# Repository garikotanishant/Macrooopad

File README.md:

# Macrooopad
A 10 key, 2 rotary encoder, macropad designed and built by me. With each key and rotary encoder being able to be addressable so I can set it to whatever command (volume, open specific app, brightness, etc). Useful for quickly doing actions.

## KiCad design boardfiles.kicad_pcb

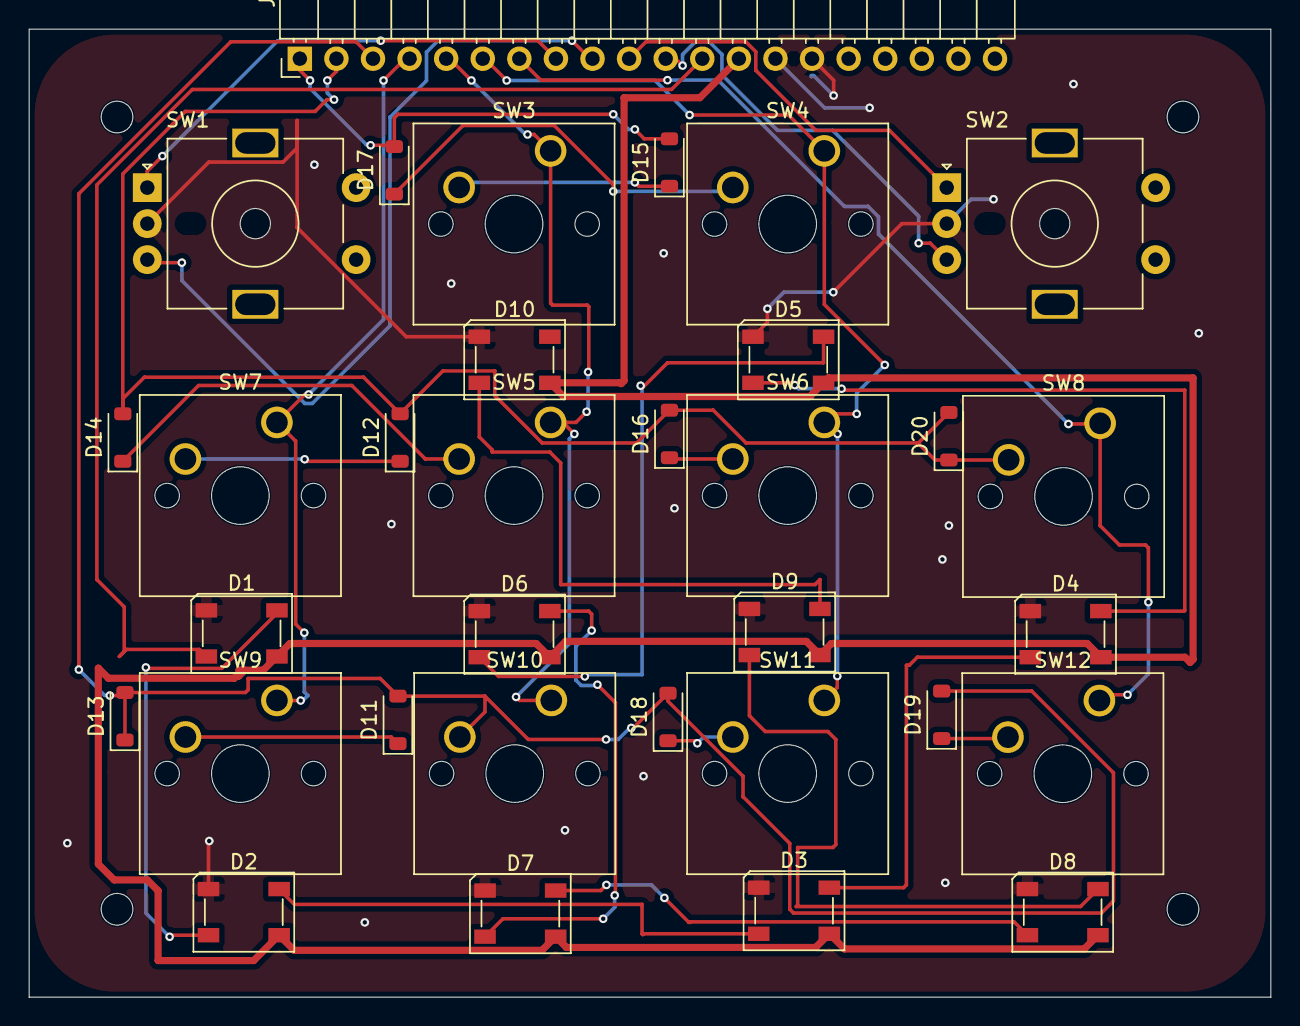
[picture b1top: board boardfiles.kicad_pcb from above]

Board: 2 copper layers, 86.2 x 67.2 mm, 33 parts (0 on the bottom side), 31 nets.

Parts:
D1, D2, D3, D4, D5, D6, D7, D8, D9, D10: SK6812; LED_SK6812_PLCC4_5.0x5.0mm_P3.2mm
D11, D12, D13, D14, D15, D16, D17, D18, D19, D20: 1N4148W; D_SOD-123
J1: Conn_01x20; PinHeader_1x20_P2.54mm_Horizontal
SW1, SW2: RotaryEncoder; RotaryEncoder_Alps_EC11E-Switch_Vertical_H20mm_MountingHoles
SW3, SW4, SW5, SW6, SW7, SW8, SW9, SW10, SW11, SW12: SW_Push; SW_Cherry_MX_1.00u_PCB

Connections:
+3V3: D1.3 (VDD), D2.3 (VDD), D3.3 (VDD), D4.3 (VDD), D5.3 (VDD), D6.3 (VDD), D7.3 (VDD), D8.3 (VDD), D9.3 (VDD), D10.3 (VDD), J1.13
/COL0: J1.4, SW7.1, SW9.1
/COL1: J1.5, SW3.1, SW5.1, SW10.1
/COL2: J1.6, SW4.1, SW6.1, SW11.1
/COL3: J1.7, SW8.1, SW12.1
/ENC_L_A: J1.8, SW1.A
/ENC_L_B: J1.9, SW1.B
/ENC_R_A: J1.10, SW2.A
/ENC_R_B: J1.11, SW2.B
/RGB: D1.2 (DIN), J1.12
/ROW0: D15.2 (A), D17.2 (A), J1.1
/ROW1: D12.2 (A), D14.2 (A), D16.2 (A), D20.1 (K), D20.2 (A), J1.2, SW8.2
/ROW2: D11.2 (A), D13.1 (K), D13.2 (A), D18.2 (A), D19.2 (A), J1.3, SW10.2
GND: D1.1 (VSS), D2.1 (VSS), D3.1 (VSS), D4.1 (VSS), D5.1 (VSS), D6.1 (VSS), D7.1 (VSS), D8.1 (VSS), D9.1 (VSS), D10.1 (VSS), J1.14, J1.15, SW1.C, SW2.C
unnamed: D1.4 (DOUT), D2.2 (DIN)
unnamed: D2.4 (DOUT), D3.2 (DIN)
unnamed: D3.4 (DOUT), D4.2 (DIN)
unnamed: D4.4 (DOUT), D5.2 (DIN)
unnamed: D5.4 (DOUT), D6.2 (DIN)
unnamed: D6.4 (DOUT), D7.2 (DIN)
unnamed: D7.4 (DOUT), D8.2 (DIN)
unnamed: D8.4 (DOUT), D9.2 (DIN)
unnamed: D9.4 (DOUT), D10.2 (DIN)
unnamed: D11.1 (K), SW9.2
unnamed: D12.1 (K), SW7.2
unnamed: D14.1 (K), SW5.2
unnamed: D15.1 (K), SW3.2
unnamed: D16.1 (K), SW6.2
unnamed: D17.1 (K), SW4.2
unnamed: D18.1 (K), SW11.2
unnamed: D19.1 (K), SW12.2

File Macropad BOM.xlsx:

Category | Qty required | Qty to Buy | References | Part/Desc | KiCad Footprint | Picked Part/MPN | Supplier | Link | Price per part | Shipping
PCB | 1.0 | 5.0 | PCB | Bare 2-layer PCB | N/A | macropad custom PCB | JLCPCB | https://cart.jlcpcb.com/quote?stencilLayer=2&stencilWidth=10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 | 2.0 | 3.3
Diode | 10.0 | 20.0 | D11, D12, D13, D14, D15, D16, D17, D18, D19, D20 | 1N4148W Switching diode | SOD-123 | DigiKey 6022450 | Digikey | 1N4148W SMC Diode Solutions | Single Diodes | DigiKey | 1.66 | 8.49
Switch | 10.0 | 12.0 | SW3, SW4, SW5, SW6, SW7, SW8, SW9, SW10, SW11, SW12 | MX-compatible mechanical keyboard switch, 1u | Cherry_MX_1.00u_PCB | K01 Switch Tactile 45g Pre-Lubed 5 Pins Hot Swap Pom Stem HMX Switches For Mx M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 | Aliexpress | https://www.aliexpress.us/item/3256809734880722.html?spm=a2g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 | 15.25 | 1.72
Keycap | 10.0 | 20.0 | Keycaps for SW3-SW12 | 1u MX-compatible keycaps | Fits Cherry MX cross stem | 20Pcs PBT Blank Keycap 1U 1X XDA Profile No Print Keycap Set for DIY Mechanical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 | Aliexpress | https://www.aliexpress.us/item/3256804794847948.html?spm=a2g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 | 4.39 | 1.72
RGB LED | 10.0 | 12.0 | D1, D2, D3, D4, D5, D6, D7, D8, D9, D10 | SK6812 addressable RGB LED | SK6812 | WS2812 SK6812 RGB Pixel Led Chip Individually Addressable WS2812B SK6812 RGBCW 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 | Aliexpress | https://www.aliexpress.us/item/3256805844520306.html?spm=a2g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 | 4.5 | 1.72
Rotary Encoder | 2.0 | 2.0 | SW1, SW2 | EC11-style rotary encoder, vertical, A/C/B pins | Alps EC11E | 2/10PCSEC11 rotary encoder Digital potentiometer, plum blossom, half axis, five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 | Aliexpress | https://www.aliexpress.us/item/3256808861665209.html?spm=a2g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 | 5.0 | 1.72
Header | 1.0 | 1.0 | J1 | 1x20 2.54mm right angle male pin header | 1x20 2.54mm Horizontal | 1x20 right angle male header | Aliexpress | https://www.aliexpress.us/item/2255800801798474.html?spm=a2g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 | 1.55 | 1.72
Cable | 1.0 | 1.0 | J1 to Pico | 20-wire Dupont/ribbon cable to external Raspberry Pi Pico | N/A | 20-pin dupont cable | Aliexpress | https://www.aliexpress.us/item/3256809464901432.html?spm=a2g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 | 2.77 | 1.72
Controller | 1.0 | 1.0 | External | Rasperry Pi Pico or compatible controller | External, not mounted on PCB | Raspberry Pi Pico Board RP2040 TYPE-C / MICRO Dual-Core 264KB ARM Low-Power Mic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 | Aliexpress | https://www.aliexpress.us/item/3256803486365836.html?spm=a2g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 | 2.97 | 1.72
Mounting | 4.0 | 4.0 | Mounting Holes | Standoffs+screws | M2 | 5-50pcs M2 M2.5 M3 M4 M5 M6 M8 DIN912 Alloy Steel Grade12.9 or 304 Hexagon Sock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 | Aliexpress | https://www.aliexpress.us/item/2251832735601754.html?spm=a2g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 | 1.69 | 1.72
 |  |  |  |  |  |  |  |  | Total: 41.78 | Total: 25.25 (with discount) |  | Combined: $67.03

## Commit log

2026-06-12 Create boardfiles
2026-06-12 Update boardfiles
2026-06-12 Create Bill of Materials
